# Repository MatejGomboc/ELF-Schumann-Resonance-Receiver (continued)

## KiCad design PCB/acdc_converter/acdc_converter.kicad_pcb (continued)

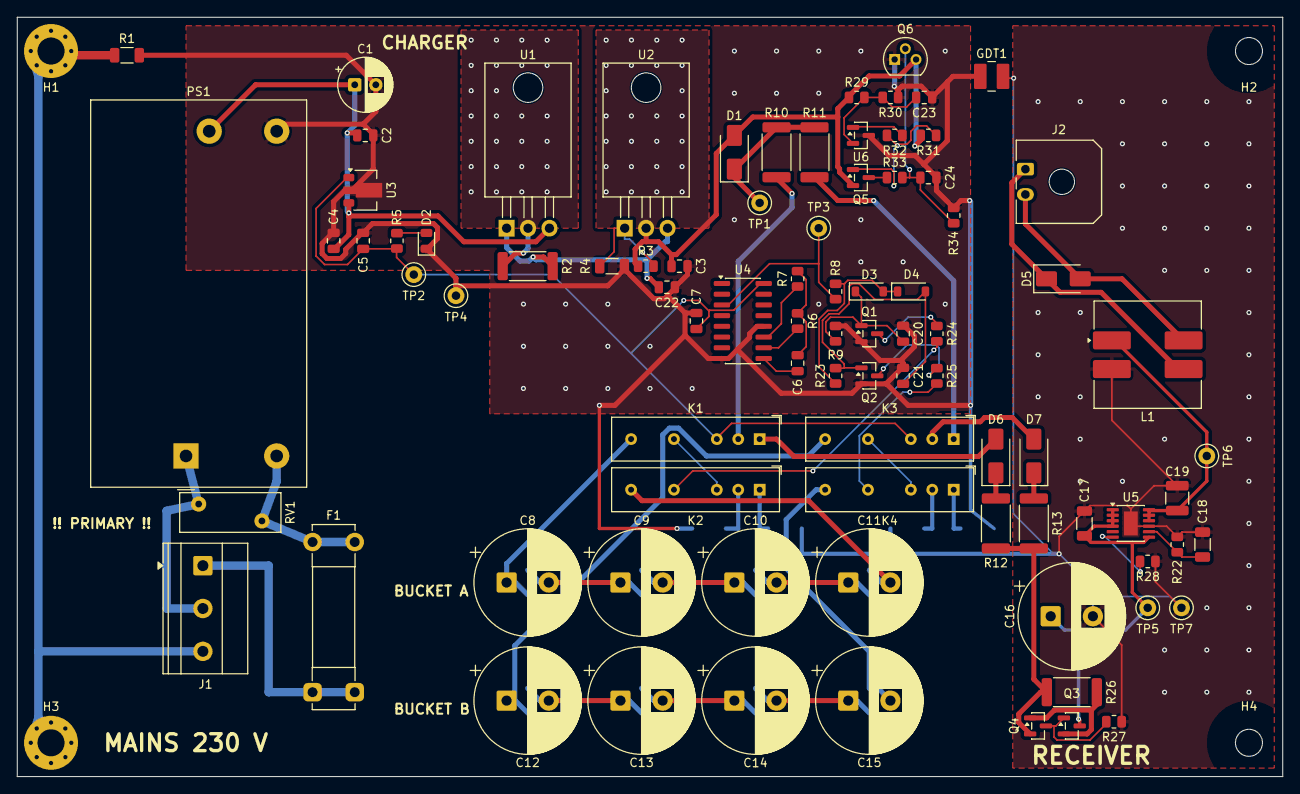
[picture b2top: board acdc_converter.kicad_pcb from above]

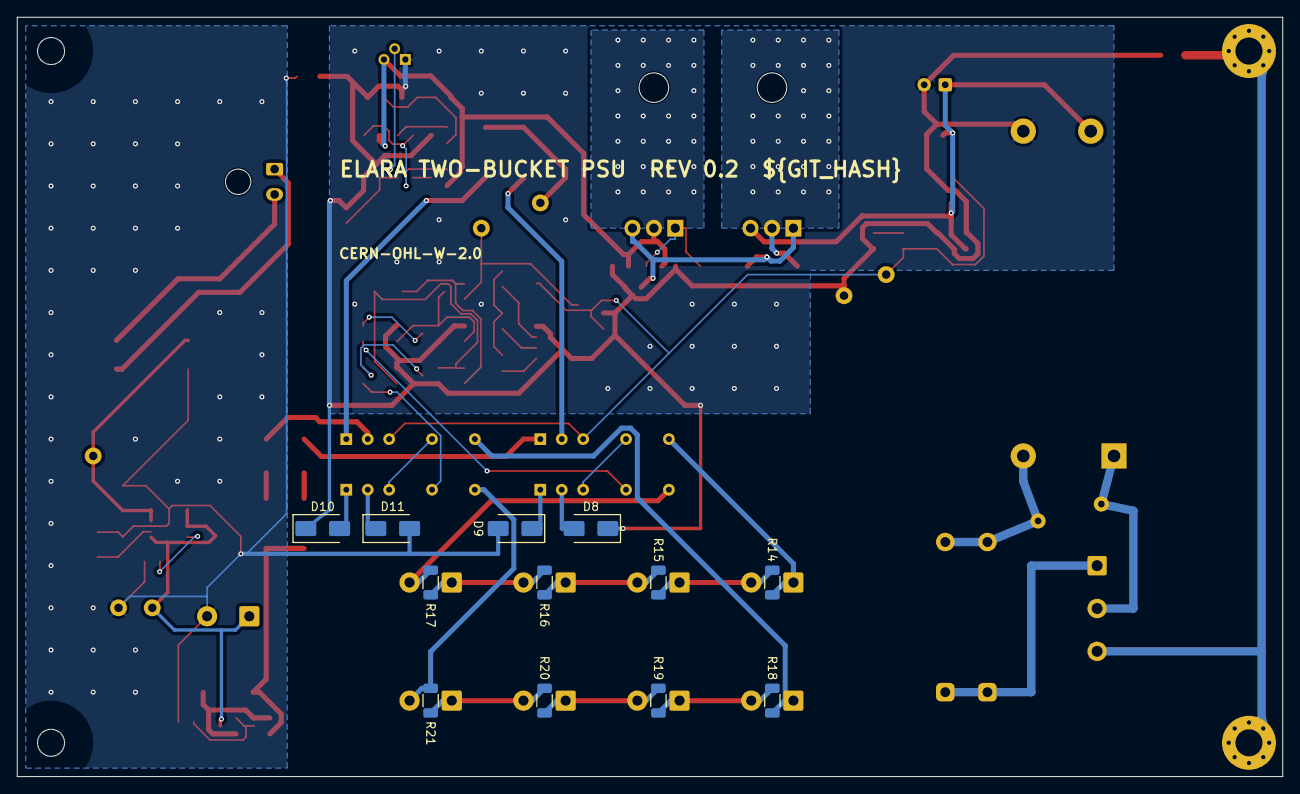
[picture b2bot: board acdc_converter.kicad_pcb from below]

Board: 2 copper layers, 150.0 x 90.0 mm, 103 parts (12 on the bottom side), 62 nets.

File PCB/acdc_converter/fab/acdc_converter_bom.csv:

"Reference","Value","Footprint","Manufacturer","MPN","Description","QUANTITY","DNP"
"C1","47u","Capacitor_THT:CP_Radial_D6.3mm_P2.50mm","Panasonic","EEU-FR1E470","Electrolytic 47u 25V low-ESR","1",""
"C2,C3,C5,C7,C22","100n","Capacitor_SMD:C_0805_2012Metric","Murata","GRM21BR71H104KA01L","MLCC 100n 50V X7R 0805","5",""
"C4","330n","Capacitor_SMD:C_0805_2012Metric","Murata","GRM21BR71H334KA88L","MLCC 330n 50V X7R 0805","1",""
"C6","10n","Capacitor_SMD:C_0805_2012Metric","Murata","GRM2195C1H103JA01D","MLCC 10n 50V C0G 0805 (Ct)","1",""
"C8-C15","10F","Capacitor_THT:CP_Radial_D12.5mm_P5.00mm","Eaton","HV1030-2R7106-R","EDLC 10 F 2.7 V, D10 x 30 mm, P5.0 (any 10 F 2.7 V radial cell; match within 5%)","8",""
"C16","2200u","Capacitor_THT:CP_Radial_D12.5mm_P5.00mm","Panasonic","EEU-FR1C222","Electrolytic 2200u 16V low-ESR, 12.5 x 20 mm, rides through the relay transit","1",""
"C17","10u","Capacitor_SMD:C_1206_3216Metric","Murata","GRM31CR71E106KA12L","MLCC 10u 25V X7R 1206","1",""
"C18","22u","Capacitor_SMD:C_1206_3216Metric","Murata","GRM31CR71C226ME15L","MLCC 22u 16V X7R 1206 (C_SET: lowest 1/f noise, ~4 s soft start)","1",""
"C19","22u","Capacitor_SMD:C_1210_3225Metric","Murata","GRM32ER71E226KE15L","MLCC 22u 25V X7R 1210 (LT3045 COUT >= 10 uF effective)","1",""
"C20,C21","220n","Capacitor_SMD:C_0805_2012Metric","Murata","GRM21BR71H224KA01L","MLCC 220n 50V X7R 0805 (gate A hold),MLCC 220n 50V X7R 0805 (gate B delay)","2",""
"D1,D6-D11","SS34","Diode_SMD:D_SMA","Vishay","SS34-E3/57T","Bucket negative leg, one way only: no charger-receiver loop through earth during reed skew or with a welded reed,Buckets diode-OR onto LOAD_P: the leaving bucket breaks with no current,Stops the buckets discharging into the charger when mains is off","7",""
"D2","GREEN","LED_SMD:LED_0805_2012Metric","Wurth","150080VS75000","LED green, mains present (charger side only)","1",""
"D3,D4","1N4148W","Diode_SMD:D_SOD-123","Diodes Inc.","1N4148W-7-F","Bucket A gate: fast on edge,Bucket B gate: fast off edge","2",""
"D5","SMAJ12A","Diode_SMD:D_SMA","Littelfuse","SMAJ12A","TVS 12 V, output clamp","1",""
"F1","T500mA","Fuse:Fuseholder_Clip-5x20mm_Bel_FC-203-22_Lateral_P17.80x5.00mm_D1.17mm_Horizontal","Littelfuse / Bel Fuse","0215.500MXP + 2x FC-203-22 clips","Fuse 5x20 mm T500 mA 250 V slow-blow, CERAMIC, 1500 A breaking (a glass 5x20 breaks only ~35 A), in PCB clips","1",""
"J1","MAINS L N PE","elara:TerminalBlock_Phoenix_MKDS-1,5-3-5.08_1x03_P5.08mm_Horizontal_Mains","Phoenix Contact","1715734","Mains input: 1 L, 2 N, 3 PE (2.3 mm pads: 2.78 mm creepage pin to pin)","1",""
"J2","DC OUT","Connector_Molex:Molex_Micro-Fit_3.0_43650-0200_1x02_P3.00mm_Horizontal","Molex","43650-0200","Micro-Fit 3.0 2-pin, 6.98 V to the antenna amplifier (shielded pair)","1",""
"K1-K4","SIL05-1C90-51D","Relay_THT:Relay_SPDT_StandexMeder_SIL_Form1C","Standex","SIL05-1C90-51D","Bucket A reed relay, SPDT 10 W 0.5 A, 1.5 pF open, 5 V 200 R coil with diode; two coils in series per bucket,Bucket B reed relay, SPDT 10 W 0.5 A, 1.5 pF open, 5 V 200 R coil with diode; two coils in series per bucket","4",""
"L1","CMC","Inductor_SMD:L_CommonModeChoke_Bourns_SRF1260","Bourns","SRF1260-102M","Common-mode choke 1 mH, keeps RF off the output cable","1",""
"PS1","IRM-05-15","Converter_ACDC:Converter_ACDC_MeanWell_IRM-05-xx_THT","Mean Well","IRM-05-15","5 W 15 V encapsulated AC-DC module, 3 kVAC, EN55032 class B","1",""
"Q1,Q2","2N7002","Package_TO_SOT_SMD:SOT-23","onsemi","2N7002LT1G","Bucket A relay coil driver,Bucket B relay coil driver","2",""
"Q3","Si2319CDS","Package_TO_SOT_SMD:SOT-23","Vishay","Si2319CDS-T1-GE3","Load-path limiter pass FET, P-ch 40 V 4.4 A, VGS +-20 V","1",""
"Q4","MMBT3906","Package_TO_SOT_SMD:SOT-23","onsemi","MMBT3906LT1G","Limiter sense: turns Q3 down above 0.6 V / 1.5 R = 0.4 A","1",""
"R1","0","Resistor_SMD:R_1206_3216Metric","Panasonic","ERJ-8GEY0R00V","Bonds charger ground to PE/enclosure: all switching noise stays in the grounded box","1",""
"R2","6.2","Resistor_SMD:R_2512_6332Metric","Vishay","CRCW25126R20FKEG","Current set 6R2 1% 1 W 2512","1",""
"R3","120","Resistor_SMD:R_0805_2012Metric","Panasonic","ERA-6AEB121V","Thin film 120 0.1% 0805","1",""
"R4","909","Resistor_SMD:R_1206_3216Metric","Panasonic","ERA-8AEB9090V","Thin film 909R 0.1% 1206 (100 mW)","1",""
"R5","4.7k","Resistor_SMD:R_0805_2012Metric","Panasonic","ERA-6AEB472V","Thin film 4.7k 0.1% 0805","1",""
"R6","80.6k","Resistor_SMD:R_0805_2012Metric","Panasonic","ERA-6AEB8062V","Thin film 80.6k 0.1% 0805","1",""
"R7","1M","Resistor_SMD:R_0805_2012Metric","Panasonic","ERA-6AEB105V","Thin film 1M 0.1% 0805","1",""
"R8","100","Resistor_SMD:R_0805_2012Metric","Panasonic","ERA-6AEB101V","Thin film 100 0.1% 0805","1",""
"R9,R27","100k","Resistor_SMD:R_0805_2012Metric","Panasonic","ERA-6AEB104V","Thin film 100k 0.1% 0805: Q3 gate pull-down (Q3 fully on below the limit),Thin film 100k 0.1% 0805: bucket A release delay with C20 (30-50 ms)","2",""
"R10,R11","2.2","Resistor_SMD:R_2512_6332Metric","Vishay","CRCW25122R20FKEG","Charger path, limits the make current","2",""
"R12,R13","1","Resistor_SMD:R_2512_6332Metric","Vishay","CRCW25121R00FKEG","Load path, damps the make current (the 0.4 A limiter Q3/Q4 caps it)","2",""
"R14-R21","5.1k","Resistor_SMD:R_1206_3216Metric","Panasonic","ERJ-8ENF5101V","Balancing 5k1 1% 1206 (~0.5 mA, >10x cell leakage)","8",""
"R22","69.8k","Resistor_SMD:R_0805_2012Metric","Panasonic","ERA-6AEB6982V","Thin film 69.8k 0.1% 0805","1",""
"R23","470k","Resistor_SMD:R_0805_2012Metric","Panasonic","ERJ-6ENF4703V","Thick film 470k 1% 0805: bucket B arrival delay with C21","1",""
"R24,R25","47","Resistor_SMD:R_0805_2012Metric","Panasonic","ERJ-6ENF47R0V","Thick film 47R 1% 0805: two 5 V coils in series from 12 V (27 mA, pull-in margin kept at 85 C)","2",""
"R26","1.5","Resistor_SMD:R_2512_6332Metric","Vishay","CRCW25121R50FKEG","Limiter sense 1R5 1% 1 W 2512 (0.4 A)","1",""
"R28","499","Resistor_SMD:R_0805_2012Metric","Panasonic","ERA-6AEB4990V","Thin film 499 0.1% 0805","1",""
"RV1","275VAC","Varistor:RV_Disc_D12mm_W4.7mm_P7.5mm","TDK","B72210S0271K101","MOV 275 VAC, mains surge clamp after the fuse","1",""
"TP1","CHG_D","TestPoint:TestPoint_Keystone_5000-5004_Miniature","Keystone","5000","Test point CHG_D","1",""
"TP2","+12V_C","TestPoint:TestPoint_Keystone_5000-5004_Miniature","Keystone","5000","Test point +12V_C","1",""
"TP3","SWAP","TestPoint:TestPoint_Keystone_5000-5004_Miniature","Keystone","5000","Test point SWAP","1",""
"TP4","GND_C","TestPoint:TestPoint_Keystone_5000-5004_Miniature","Keystone","5001","Test point GND_C","1",""
"TP5","LOAD_P","TestPoint:TestPoint_Keystone_5000-5004_Miniature","Keystone","5000","Test point LOAD_P","1",""
"TP6","VREG","TestPoint:TestPoint_Keystone_5000-5004_Miniature","Keystone","5000","Test point VREG","1",""
"TP7","GND","TestPoint:TestPoint_Keystone_5000-5004_Miniature","Keystone","5001","Test point GND","1",""
"U1,U2","LM317","Package_TO_SOT_THT:TO-220-3_Horizontal_TabDown","onsemi","LM317BTG","Constant current, 1.25 V / 6.2 R = 0.2 A (tab = OUT = CC_SET, on a copper area); B grade, -40 C,Constant voltage 1.25 V x (1 + 909/120) + 50 uA x 909 = 10.76 V (two SS34s to the cells); the 10.5 mA divider keeps the LM317 above its 10 mA minimum load (tab bolted to the base)","2",""
"U3","L78L12","Package_TO_SOT_SMD:SOT-89-3","STMicroelectronics","L78L12ABUTR","12 V for the relay coils and timer; B grade, -40 C","1",""
"U4","CD4060B","Package_SO:SOIC-16_3.9x9.9mm_P1.27mm","Texas Instruments","CD4060BM96","14-stage counter + RC oscillator, f = 1/(2.3 Rt Ct) = 540 Hz, Q14 toggles every ~15 s","1",""
"U5","LT3045","Package_SO:MSOP-12-1EP_3x4.039mm_P0.65mm_EP1.651x2.845mm","Analog Devices","LT3045EMSE#PBF","Ultralow-noise LDO: EN and PGFB tied to IN (no fast start-up), ILIM 499 R (~0.3 A)","1",""

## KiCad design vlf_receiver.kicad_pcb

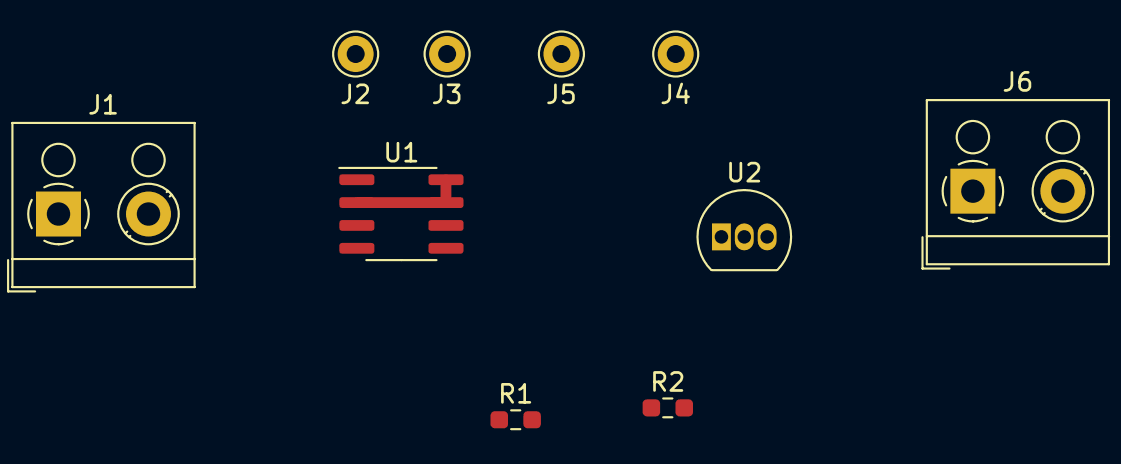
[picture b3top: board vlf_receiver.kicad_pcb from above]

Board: 2 copper layers, 10 parts (0 on the bottom side), 6 nets.

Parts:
J1: OUT; TerminalBlock_RND_205-00001_1x02_P5.00mm_Horizontal
J2: ANT+; Pin_D1.0mm_L10.0mm
J3: ANT-; Pin_D1.0mm_L10.0mm
J4: BLEED-R; Pin_D1.0mm_L10.0mm
J5: FILT-C; Pin_D1.0mm_L10.0mm
J6: VCC; TerminalBlock_RND_205-00001_1x02_P5.00mm_Horizontal
R1: 100k; R_0603_1608Metric_Pad0.98x0.95mm_HandSolder
R2: 10k; R_0603_1608Metric_Pad0.98x0.95mm_HandSolder
U1: LMP7721; SOIC-8_3.9x4.9mm_P1.27mm
U2: TLE2426xLP; TO-92_Inline

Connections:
+2V5: J1.1, J3.1, J4.1, J5.1, R2.1, U2.1
+5V: J6.1, U1.6, U2.3
GND: J6.2, U1.3, U2.2
unnamed: J1.2, R1.2, U1.4
unnamed: J2.1, U1.1
unnamed: R1.1, R2.2, U1.2, U1.7, U1.8

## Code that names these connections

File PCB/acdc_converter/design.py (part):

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           footprint='elara:TerminalBlock_Phoenix_MKDS-1,5-3-5.08_1x03_P5.08mm_Horizontal_Mains',
           fields={'Manufacturer': 'Phoenix Contact', 'MPN': '1715734',
                   'Description': 'Mains input: 1 L, 2 N, 3 PE (2.3 mm pads: 2.78 mm creepage pin to pin)'})
    f1 = sh.add('F1', 'Device:Fuse', 'T500mA', (55.88, 35.56), {1: 'L_IN', 2: 'AC_L'}, rot=90,
           footprint='Fuse:Fuseholder_Clip-5x20mm_Bel_FC-203-22_Lateral_P17.80x5.00mm_D1.17mm_Horizontal',
           fields={'Manufacturer': 'Littelfuse / Bel Fuse', 'MPN': '0215.500MXP + 2x FC-203-22 clips',
                   'Description': 'Fuse 5x20 mm T500 mA 250 V slow-blow, CERAMIC, 1500 A breaking '
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    sh.add('U1', 'Regulator_Linear:LM317_TO-220', 'LM317', (210.82, 38.1),
           {3: '+15V_C', 2: 'CC_SET', 1: 'CC_OUT'}, footprint='Package_TO_SOT_THT:TO-220-3_Horizontal_TabDown',
           fields={'Manufacturer': 'onsemi', 'MPN': 'LM317BTG',
                   'Description': 'Constant current, 1.25 V / 6.2 R = 0.2 A (tab = OUT = CC_SET, on a copper area); B grade, -40 C'})
    R(sh, '6.2', (210.82, 60.96), 'CC_SET', 'CC_OUT', rot=90, fp=R2512,
      fields={'Manufacturer': 'Vishay', 'MPN': 'CRCW25126R20FKEG', 'Description': 'Current set 6R2 1% 1 W 2512'})
    sh.add('U2', 'Regulator_Linear:LM317_TO-220', 'LM317', (251.46, 38.1),
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    C(sh, '330n', (322.58, 60.96), '+15V_C', 'GND_C', fields=mur('GRM21BR71H334KA88L', 'MLCC 330n 50V X7R 0805'))
    C(sh, '100n', (347.98, 60.96), '+12V_C', 'GND_C')
    r5 = R(sh, '4.7k', (368.3, 45.72), '+12V_C', 'LED_C')
    d2 = sh.add('D2', 'Device:LED', 'GREEN', (368.3, 68.58), {2: 'LED_C', 1: 'GND_C'}, rot=90,
                fields_at={'Reference': (-3.3, -0.5, 'left'), 'Value': (-3.3, 2.0, 'left')},
           footprint='LED_SMD:LED_0805_2012Metric',
           fields={'Manufacturer': 'Wurth', 'MPN': '150080VS75000',
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           footprint='Package_SO:SOIC-16_3.9x9.9mm_P1.27mm',
           fields={'Manufacturer': 'Texas Instruments', 'MPN': 'CD4060BM96',
                   'Description': '14-stage counter + RC oscillator, f = 1/(2.3 Rt Ct) = 540 Hz, Q14 toggles every ~15 s'})
    C(sh, '10n', (91.44, 124.46), 'OSC_C', 'OSC_X', rot=90,
      fields=mur('GRM2195C1H103JA01D', 'MLCC 10n 50V C0G 0805 (Ct)'))
    R(sh, '80.6k', (91.44, 139.7), 'OSC_R', 'OSC_X', rot=90)
    R(sh, '1M', (91.44, 154.94), 'OSC_I', 'OSC_X', rot=90)
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    r30 = R(sh, '10k', (119.38, 149.86), 'CB_REF', 'GND_C',
            fields=pana('ERA-6AEB103V', 'Thin film 10k 0.1% 0805: crowbar divider bottom'))
    c23 = C(sh, '100n', (129.54, 149.86), 'CB_REF', 'GND_C', fields_at={'Reference': (1.905, -1.27, 'left'), 'Value': (1.905, 1.27, 'left')})
    u6 = sh.add('U6', 'Reference_Voltage:TL431DBZ', 'TL431B', (144.78, 160.02), {1: 'CB_K', 2: 'CB_REF', 3: 'GND_C'}, rot=90,
                fields_at={'Reference': (-1.27, -10.16, 'left'), 'Value': (-1.27, -7.62, 'left')},
                footprint='Package_TO_SOT_SMD:SOT-23',
                fields={'Manufacturer': 'Texas Instruments', 'MPN': 'TL431BIDBZR',
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
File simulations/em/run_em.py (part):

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# 3. Magnetic loops
# ===========================================================================
def board_loop(board):
    """Projected area (xy) of the input loop on the board: J201 -> IN_P -> U201 pin 1,
    pin 8 -> IN_N spine -> R202 (Rg) -> CG track -> C202 (Cg) -> GND, closed by a
    straight return in the GND plane back to J201."""
    pads = {(pd["ref"], pd["num"]): (pd["x"], pd["y"]) for pd in board["pads"]}
    # follow the CG track from R202 to C202 through the segment graph
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    ax.set_aspect("equal")
    cb = fig.colorbar(im, ax=ax, fraction=0.04, pad=0.02)
    cb.ax.tick_params(colors=SUBTLE, labelsize=8)
    cb.set_label("V, 0.25 mm above F.Cu (IN_P = 1 V)", color=SUBTLE, fontsize=8)
    for net, col in colours.items():
        ax.plot([], [], color=col, label=short(net))
    legend(ax, loc="lower left", ncol=2)
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    ax.set_yticks(yy)
    ax.set_yticklabels(nets, color=TEXT, fontsize=8)
    ax.invert_yaxis()
    labels(ax, "Capacitance from IN_P (3-D solve)", "C (fF)", "")
    legend(ax, loc="lower right")
    # (d) injected level vs floor, as built
    ax = fig.add_subplot(gs[1, 1])
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    ax.set_yticklabels([n for n, _ in items], color=TEXT, fontsize=8)
    ax.invert_yaxis()
    ax.set_xscale("log")
    labels(ax, "Nearest approach to IN_P copper (edge to edge, GUARD touches)", "distance (mm)", "")
    fig.suptitle("ELARA -- electrostatic coupling into the guarded input (PCB as built)", color=TEXT, fontsize=13, x=0.01, ha="left")
    save(fig, "em_guard_coupling.svg")

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    ax.axhline(MAINS_PICKUP[1], color=YELLOW, ls=":")
    ax.axhline(floor_ant(50.0) * math.sqrt(BIN), color=GREY, ls="-.", label="noise in a 0.1 Hz bin at 50 Hz")
    ax.set_ylim(1e-13, 1e-1)
    labels(ax, "50 Hz E-field reaching IN_P through the shield", "E-field at the shield (V/m rms)", "V at IN_P (V rms)")
    legend(ax, loc="lower right")
    fig.suptitle("ELARA -- aluminium shield: transparent to ELF H, opaque to E", color=TEXT, fontsize=13, x=0.01, ha="left")
    save(fig, "em_shielding.svg")
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    for (k, a), col in zip(mag["loops_m2"].items(), cols):
        ax.loglog(b * 1e6, w * b * a, color=col, label=f"{k}: {a * 1e6:.0f} mm²")
    ax.loglog(b * 1e6, w * b * mag["cable"]["dm_area_m2"], color=ORANGE, ls="--", label="AES3 pair, differential")
    ax.loglog(b * 1e6, w * b * mag["cable"]["cm_area_m2"], color=RED, ls="--", label="AES3 cable vs earth, common mode (100 m; at the transformer, not at IN_P)")
    ax.axhline(clip, color=RED, lw=0.8, label=f"clip level {clip * 1e3:.0f} mV")
    ax.axhline(MAINS_PICKUP[0], color=YELLOW, ls=":", label="antenna mains E pickup 1-5 mV")
    ax.axhline(floor_ant(50) * math.sqrt(BIN), color=GREY, ls="-.", label="noise, 0.1 Hz bin")
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    ps = mag["psu"]
    f = np.logspace(-2, 2, 400)
    # relay switching: two impulses of flux phi per 30.4 s period -> lines every 1/30.4 Hz
    ax.loglog(f, np.full_like(f, ps["line_rms_V"]), color=ORANGE, label="relay coil edges: each swap line (rms)")
    ax.loglog(f, np.full_like(f, ps["charger_flux_Vs"] * 2 / 30.38), color=PURPLE, label="charger/load loop step: each line")
    ax.loglog(f, floor_ant(np.clip(f, 7.83, 45)) * math.sqrt(BIN), color=GREY, ls="-.", label="receiver noise, 0.1 Hz bin")
    ax.scatter([50], [ps["irm_50Hz_emf_V"]], color=RED, zorder=5, label="IRM-05 50 Hz input-current field")
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    y = np.arange(len(keys))
    ax.barh(y - 0.2, v_rf, height=0.38, color=ORANGE, label="RF amplitude at IN+ (V peak)")
    ax.barh(y + 0.2, np.maximum(v_dc, 1e-30), height=0.38, color=PURPLE, label=f"rectified shift (EMIRR {EMIRR_DB:.0f} dB; DC for a steady clock)")
    ax.axvline(floor_ant(7.83) * math.sqrt(BIN) * 0.583, color=GREY, ls="-.", label="IN_P noise in a 0.1 Hz bin")
    ax.set_xscale("log")
    ax.set_yticks(y)
    ax.set_yticklabels(keys, color=TEXT, fontsize=8)
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
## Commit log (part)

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2021-04-08 V2 initial commit.
2021-04-08 Removed redundant files.
2021-04-08 Updated schematic.
2021-04-08 Updated ignore list.
2021-04-09 Update.
2026-03-15 Initial commit of AI augmented design branch.
2026-03-15 Added .gitkeep to .venv
2026-03-15 Updated .gitignore
2026-03-15 Added capacitor_square KiCAD project.
2026-03-20 Gitignore Claude Code local settings
2026-03-20 Regenerate plate capacitor plot (air-gap only)
